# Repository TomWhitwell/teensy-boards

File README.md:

# teensy-boards

## Teensy 3.1 Breakout Board R2

[https://www.oshpark.com/shared_projects/ttl7D5iT](https://www.oshpark.com/shared_projects/ttl7D5iT)

## Teensy 3.2 Breakout Board R3

[https://www.oshpark.com/shared_projects/Gnvbt7io](https://www.oshpark.com/shared_projects/Gnvbt7io)

## Teensy 3.X to 2.2" display adapter T1

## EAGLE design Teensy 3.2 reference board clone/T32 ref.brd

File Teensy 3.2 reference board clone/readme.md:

# Teensy 3 reference board clone

Teensy3 reference board recreated in eagle

shared basket at mouser: http://www.mouser.com/ProjectManager/ProjectDetail.aspx?AccessID=719df5721e

Pre-programmed Bootloader Chip for DIY Teensy LC & 3.2 Projects http://pjrc.com/store/ic_mkl02.html (IC_MKL04Z32_TQFP32)

shared project on osh park: https://www.oshpark.com/shared_projects/h2HB6bQQ

### What is different from the "original" Teensy 3.2 DIY Reference Board

PJRC Teensy 3.2 DIY Reference Board https://www.oshpark.com/shared_projects/d3J03Zeb

- the silkscreen is a bit messed up  
  
- the actuator from the tactile switch is shorter (ALPS	SKHHPKA010)

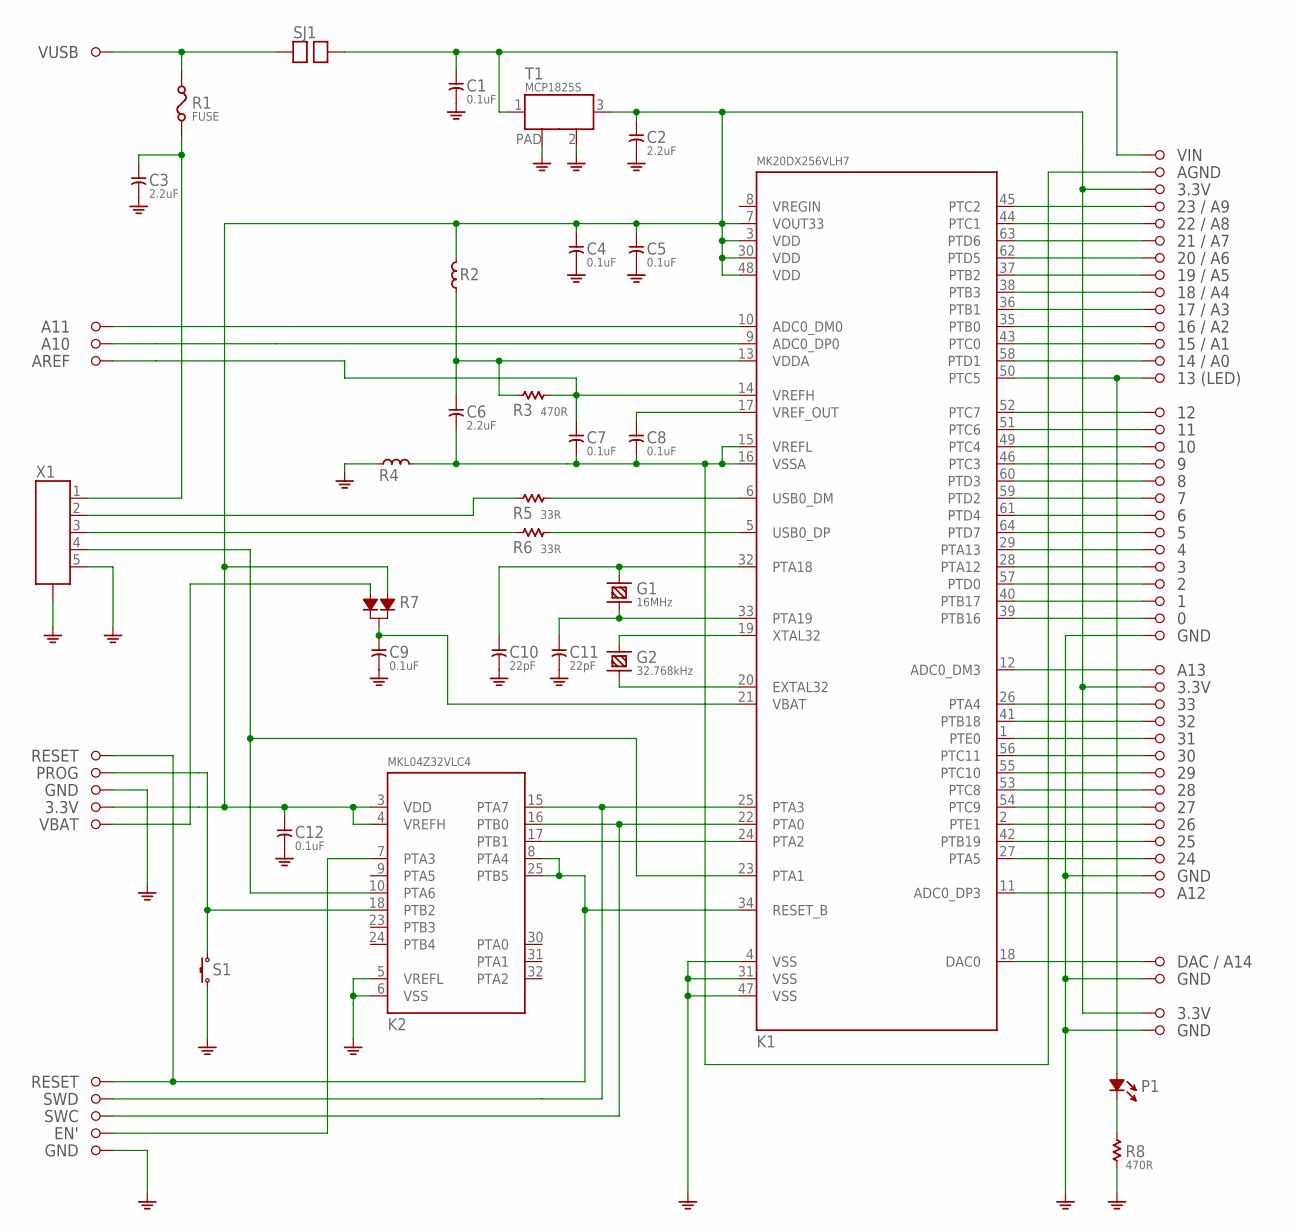
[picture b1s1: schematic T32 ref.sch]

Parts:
C1, C4, C5, C7, C8, C9, C12: 0.1uF; C0603
C2, C3, C6: 2.2uF; C0805
C10, C11: 22pF; C0603
G1: 16MHz; HC49US
G2: 32.768kHz; TC26H
K1: MK20DX256VLH7; LQFP64-05
K2: MKL04Z32VLC4; LQFP32-08
P1: LED; LED-0805
R1: FUSE; F0805
R2, R4: FERRITE; L0603
R3, R8: 470R; R0603
R5, R6: 33R; R0603
R7: DIODE_DUAL; SOT-23
S1: TACT_SWITCH; ALPS_SKHH
SJ1: SOLDERJUMPER
SX1, SX2, SX3, SX4, SX5, SX6, SX7, SX8, SX9, SX10, SX11, SX12, SX13, SX14, SX15, SX16, SX17, SX18, SX19, SX20, SX21, SX22, SX23, SX24, SX25, SX26, SX27, SX28, SX29, SX30, SX31, SX32, SX33, SX34, SX35, SX36, SX37, SX38, SX39, SX40, SX41, SX42, SX43, SX44, SX45, SX46, SX47, SX48, SX49, SX50, SX51, SX52, SX53, SX54, SX55, SX56, SX57, SX58, SX59, SX60: PIN; PTH_39MIL
T1: MCP1825S; SOT-223
X1: MINI-USB; MOLEX_SD-67503-010

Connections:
GND: C1.2, C2.2, C3.2, C4.2, C5.2, C9.2, C10.2, C11.2, C12.2, K1.4 (VSS), K1.31 (VSS), K1.47 (VSS), K2.5 (VREFL), K2.6 (VSS), R4.1, R8.1, S1.3, S1.4 (3), SX32.1, SX42.1, SX50.1, SX53.1, SX55.1, SX60.1, T1.2 (GND), T1.PAD, X1.5, X1.P$1 (CASE), X1.P$2 (CASE), X1.P$3 (CASE), X1.P$4 (CASE), X1.P$5 (CASE), X1.P$6 (CASE)
unnamed: K2.7 (PTA3), SX59.1
unnamed: K1.22 (PTA0), K2.16 (PTB0), SX58.1
unnamed: K1.24 (PTA2), K2.17 (PTB1)
unnamed: C10.1, G1.1, K1.32 (PTA18)
unnamed: C11.1, G1.2, K1.33 (PTA19)
unnamed: G2.2 (1), K1.19 (XTAL32)
unnamed: G2.1 (2), K1.20 (EXTAL32)
unnamed: K2.18 (PTB2), S1.1, S1.2 (1), SX40.1
unnamed: K1.5 (USB0_DP), R6.2
unnamed: C8.1, K1.17 (VREF_OUT)
unnamed: K1.34 (RESET_B), K2.8 (PTA4), K2.25 (PTB5), SX38.1, SX56.1
unnamed: C7.1, K1.14 (VREFH), R3.2, SX16.1
unnamed: K1.6 (USB0_DM), R5.2
unnamed: C6.1, K1.13 (VDDA), R2.1, R3.1
unnamed: R6.1, X1.3
unnamed: R5.1, X1.2
unnamed: C3.1, R1.1, X1.1
unnamed: K1.23 (PTA1), K2.10 (PTA6), X1.4
unnamed: K1.45 (PTC2), SX5.1
unnamed: K1.44 (PTC1), SX6.1
unnamed: K1.63 (PTD6), SX7.1
unnamed: K1.62 (PTD5), SX8.1
unnamed: K1.37 (PTB2), SX9.1
unnamed: K1.38 (PTB3), SX10.1
unnamed: K1.36 (PTB1), SX11.1
unnamed: K1.35 (PTB0), SX13.1
unnamed: K1.43 (PTC0), SX15.1
unnamed: K1.58 (PTD1), SX17.1
unnamed: K1.50 (PTC5), P1.+, SX18.1
unnamed: K1.52 (PTC7), SX19.1
unnamed: K1.51 (PTC6), SX20.1
unnamed: K1.49 (PTC4), SX21.1
unnamed: K1.46 (PTC3), SX22.1
unnamed: K1.60 (PTD3), SX23.1
unnamed: K1.59 (PTD2), SX24.1
unnamed: K1.61 (PTD4), SX25.1
unnamed: K1.64 (PTD7), SX26.1
unnamed: K1.29 (PTA13), SX27.1
unnamed: K1.28 (PTA12), SX28.1
unnamed: K1.57 (PTD0), SX29.1
unnamed: K1.40 (PTB17), SX30.1
unnamed: K1.39 (PTB16), SX31.1
unnamed: K1.12 (ADC0_DM3), SX33.1
unnamed: K1.26 (PTA4), SX35.1
unnamed: K1.41 (PTB18), SX36.1
unnamed: K1.1 (PTE0), SX37.1
unnamed: K1.56 (PTC11), SX39.1
unnamed: K1.55 (PTC10), SX41.1
unnamed: K1.53 (PTC8), SX43.1
unnamed: P1.-, R8.2
unnamed: C6.2, C7.2, C8.2, K1.15 (VREFL), K1.16 (VSSA), R4.2, SX3.1
unnamed: K1.18 (DAC0), SX52.1
unnamed: K1.11 (ADC0_DP3), SX51.1
unnamed: K1.27 (PTA5), SX49.1
unnamed: K1.42 (PTB19), SX48.1
unnamed: K1.2 (PTE1), SX47.1
unnamed: K1.54 (PTC9), SX45.1
unnamed: C1.1, SJ1.2, SX2.1, T1.1 (IN)
unnamed: R7.2, SX46.1
unnamed: K1.10 (ADC0_DM0), SX12.1
unnamed: K1.9 (ADC0_DP0), SX14.1
unnamed: R1.2, SJ1.1, SX1.1
unnamed: C9.1, K1.21 (VBAT), R7.3
unnamed: C2.1, C4.1, C5.1, C12.1, K1.3 (VDD), K1.7 (VOUT33), K1.30 (VDD), K1.48 (VDD), K2.3 (VDD), K2.4 (VREFH), R2.2, R7.1, SX4.1, SX34.1, SX44.1, SX54.1, T1.3 (OUT)
unnamed: K1.25 (PTA3), K2.15 (PTA7), SX57.1

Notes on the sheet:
VIN
AGND
3.3V
23 / A9
22 / A8
21 / A7
20 / A6
19 / A5
18 / A4
17 / A3
16 / A2
15 / A1
14 / A0
13 (LED)
GND
A13
A12
DAC / A14
VBAT
RESET
PROG
A11
A10
AREF
VUSB
SWD
SWC
EN'

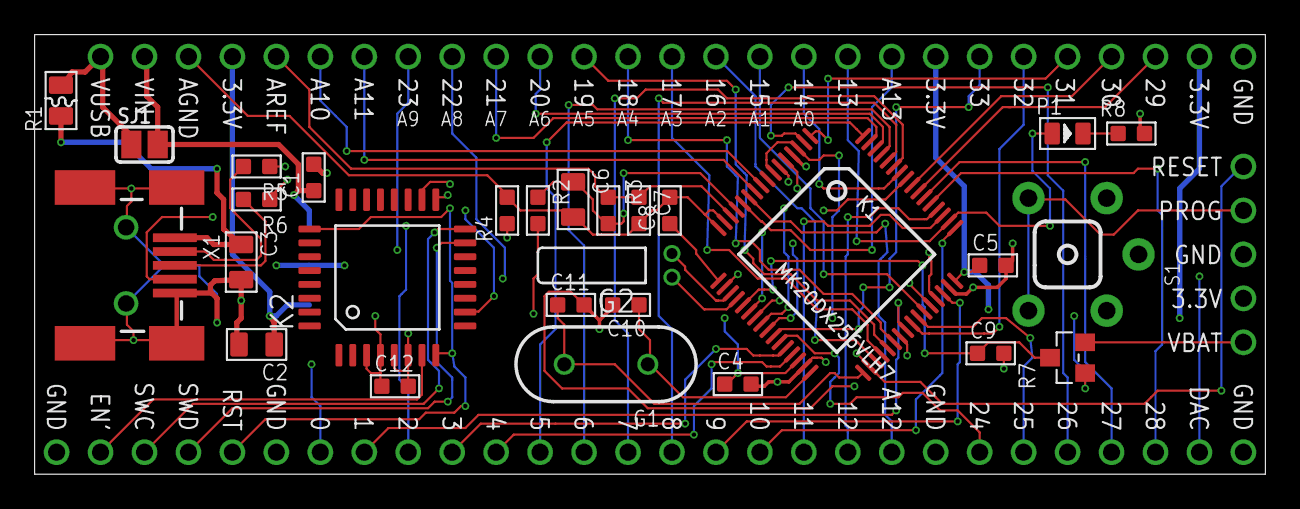
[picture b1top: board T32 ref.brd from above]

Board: 4 copper layers, 71.1 x 25.4 mm, 89 parts (1 on the bottom side), 66 nets.

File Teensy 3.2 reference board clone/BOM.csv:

"Part","TYPE","DESC","PACKAGE","MF","MPN","OC_MOUSER"
"C1","Capacitor","0.1uF / 10VDC /  X7R ","0603","Murata Electronics","GRM155R71A104KA01D","81-GRM155R71A104KA1D"
"C2","Capacitor","2.2uF / 25 VDC / X7R ","0805","Taiyo Yuden","TMK212B7225KG-TR","963-TMK212B7225KG-TR"
"C3","Capacitor","2.2uF / 25 VDC / X7R ","0805","Taiyo Yuden","TMK212B7225KG-TR","963-TMK212B7225KG-TR"
"C4","Capacitor","0.1uF / 10VDC /  X7R ","0603","Murata Electronics","GRM155R71A104KA01D","81-GRM155R71A104KA1D"
"C5","Capacitor","0.1uF / 10VDC /  X7R ","0603","Murata Electronics","GRM155R71A104KA01D","81-GRM155R71A104KA1D"
"C6","Capacitor","2.2uF / 25 VDC / X7R ","0805","Taiyo Yuden","TMK212B7225KG-TR","963-TMK212B7225KG-TR"
"C7","Capacitor","0.1uF / 10VDC /  X7R ","0603","Murata Electronics","GRM155R71A104KA01D","81-GRM155R71A104KA1D"
"C8","Capacitor","0.1uF / 10VDC /  X7R ","0603","Murata Electronics","GRM155R71A104KA01D","81-GRM155R71A104KA1D"
"C9","Capacitor","0.1uF / 10VDC /  X7R ","0603","Murata Electronics","GRM155R71A104KA01D","81-GRM155R71A104KA1D"
"C10","Capacitor","22pF / 50VDC / C0G (NP0)","0603","Vishay / Vitramon","VJ0603A220JXACW1BC","77-VJ0603A220JXACBC"
"C11","Capacitor","22pF / 50VDC / C0G (NP0)","0603","Vishay / Vitramon","VJ0603A220JXACW1BC","77-VJ0603A220JXACBC"
"C12","Capacitor","0.1uF / 10VDC /  X7R ","0603","Murata Electronics","GRM155R71A104KA01D","81-GRM155R71A104KA1D"
"G1","Crystal","16MHz / 18pF / 10ppm","HC-49US","ABRACON","ABL-16.000MHz-B1U","815-ABL-16-B1U"
"G2","Crystal","32.768kHz / 12.5pF / 20ppm","TC-26H","Citizen FineDevice"," CFS206-32.768KDZF-UB","695-CFS206-327KF-U"
"K1","Microcontroller","MK20DX256VLH7","LQFP-64","NXP","MK20DX256VLH7","841-MK20DX256VLH7"
"K2","Microcontroller","MKL04Z32VLC4 (preprogrammed)","LQFP-32","PJRC","IC_MKL04Z32_TQFP32",
"P1","LED","orange","0805","ROHM Semiconductor","SML-211DTT86","755-SML-211DTT86"
"R1","PPTC","6V / 0.5A","0805","Bel Fuse","0ZCK0050FF2E","530-0ZCK0050FF2E"
"R2","Ferrite","600R / 100MHz","0603","Murata Electronics"," BLM18AG601SN1D","81-BLM11A601S"
"R3","Resistor","470R / 1 % /  0.1 W","0603","Vishay","CRCW0603470RFKEA","71-CRCW0603-470-E3"
"R4","Ferrite","600R / 100MHz","0603","Murata Electronics"," BLM18AG601SN1D","81-BLM11A601S"
"R5","Resistor","33R / 1% / 0.25 W","0603","Panasonic","ERJ-PA3F33R0V","667-ERJ-PA3F33R0V"
"R6","Resistor","33R / 1% / 0.25 W","0603","Panasonic","ERJ-PA3F33R0V","667-ERJ-PA3F33R0V"
"R7","Diode","Dual Schottky, common cat","SOT-23","NXP Semiconductors","BAT54C,215","771-BAT54C-T/R"
"R8","Resistor","470R / 1 % /  0.1 W","0603","Vishay","CRCW0603470RFKEA","71-CRCW0603-470-E3"
"S1","Tactile switch","SPST","6x6x5 MM","ALPS","SKHHPKA010","688-SKHHPK"
"T1","Voltage regulator","3.3V 500mA","SOT-223-3","Microchip Technology","MCP1825S-3302E/DB","579-MCP1825S-3302EDB"
"X1","Mini USB","MINI USB",,"MOLEX","675031020","538-67503-1020"

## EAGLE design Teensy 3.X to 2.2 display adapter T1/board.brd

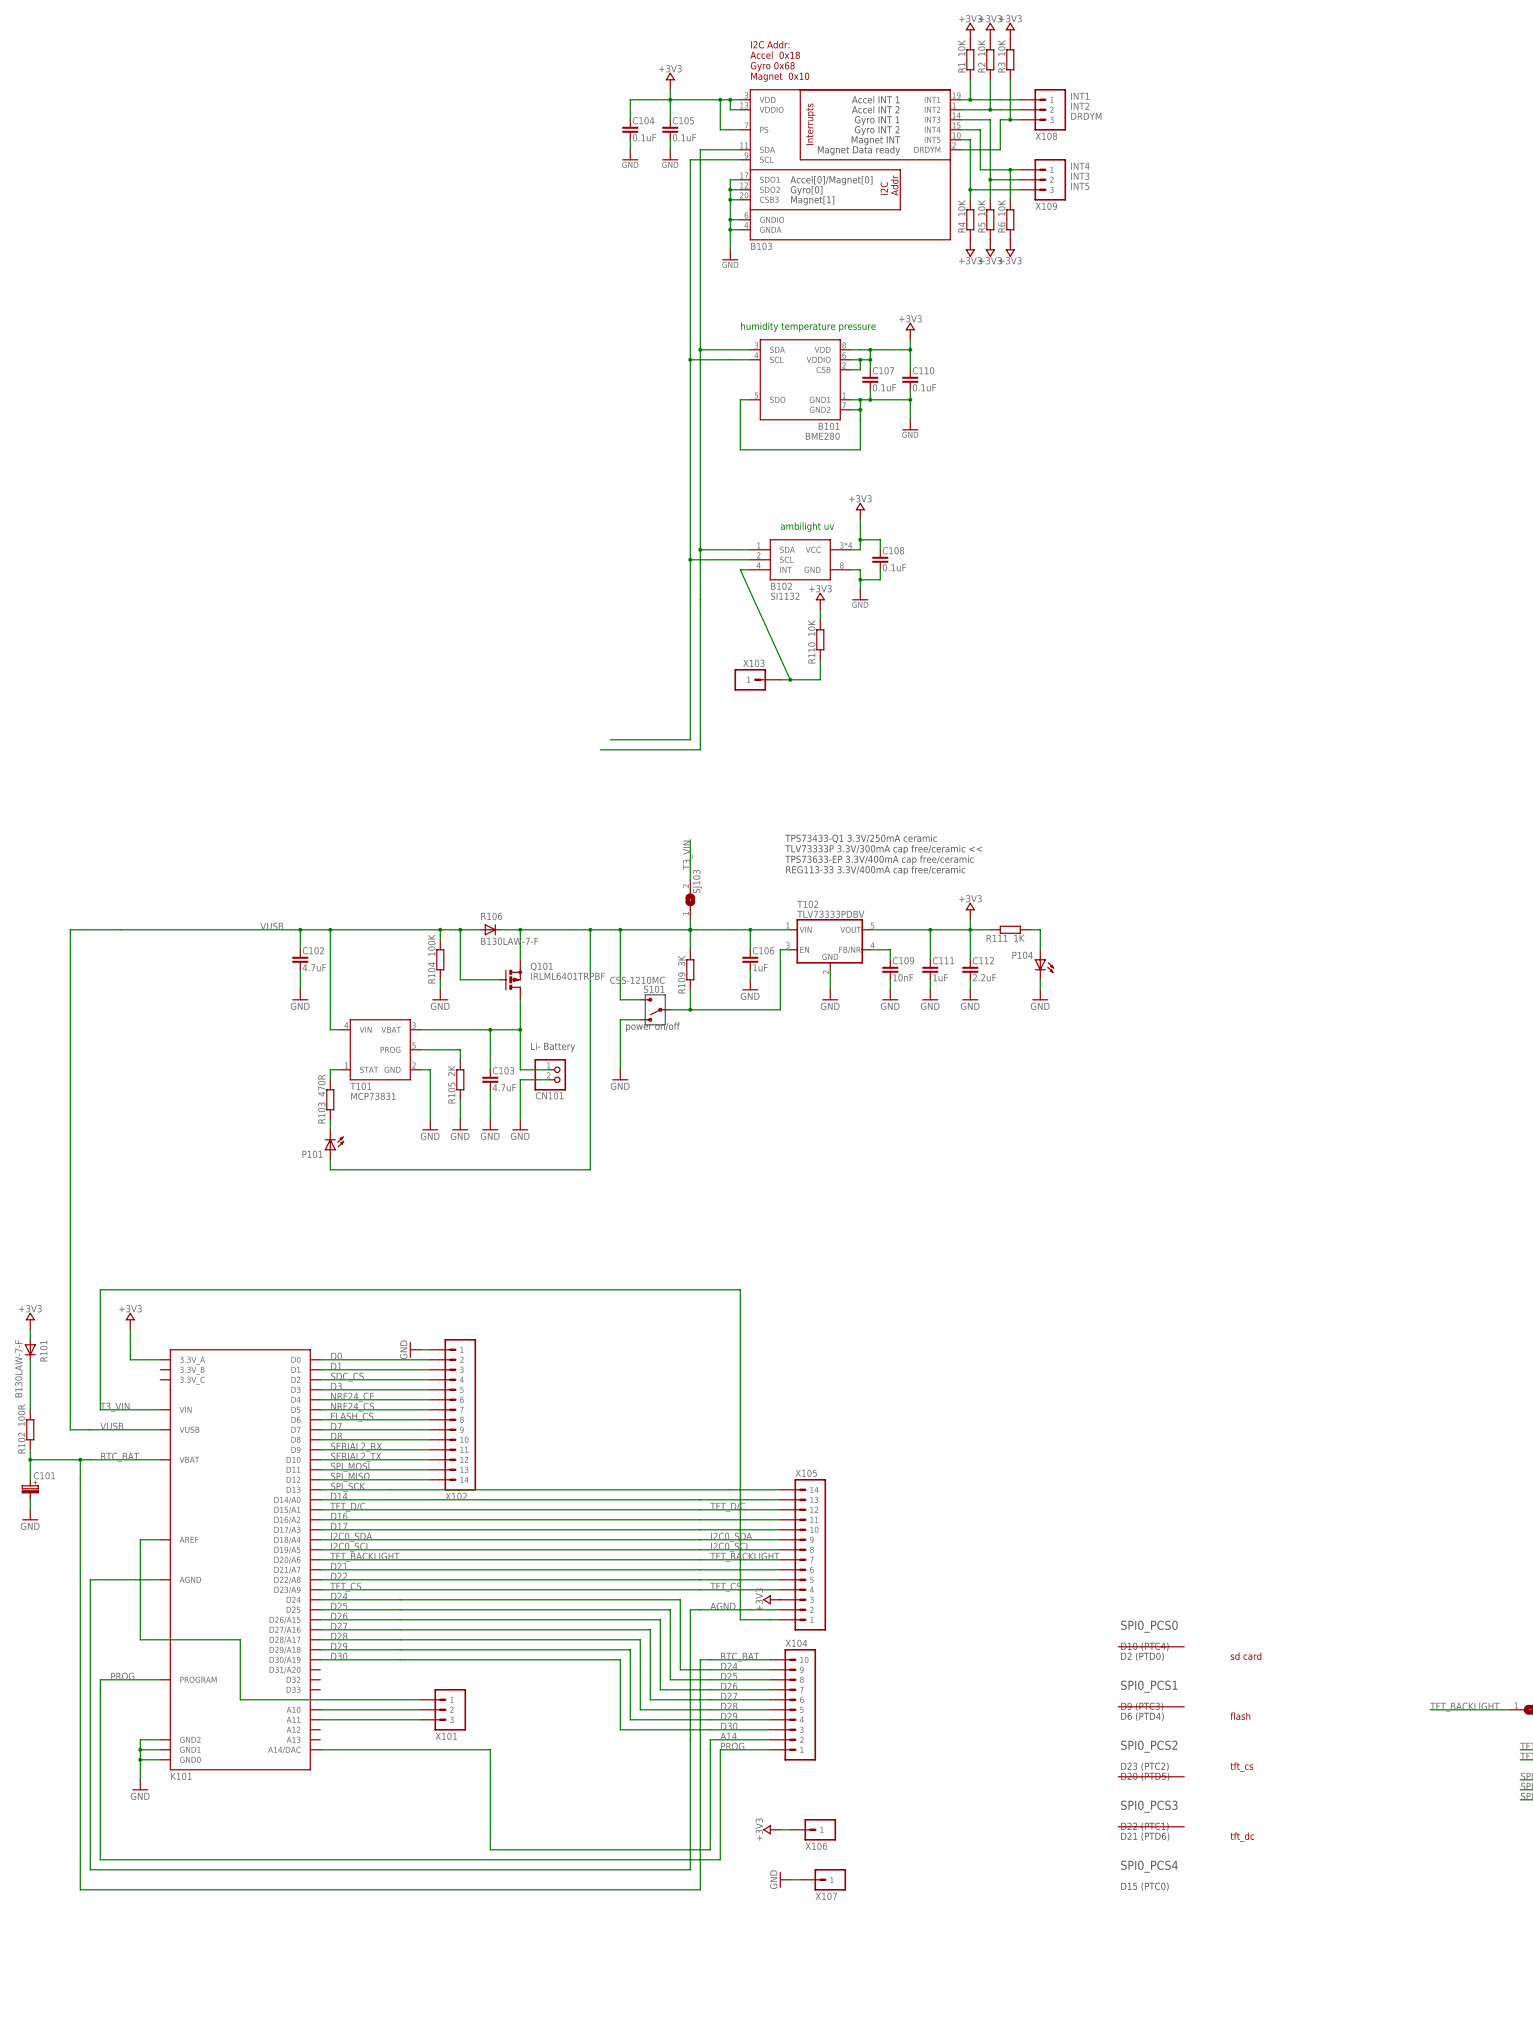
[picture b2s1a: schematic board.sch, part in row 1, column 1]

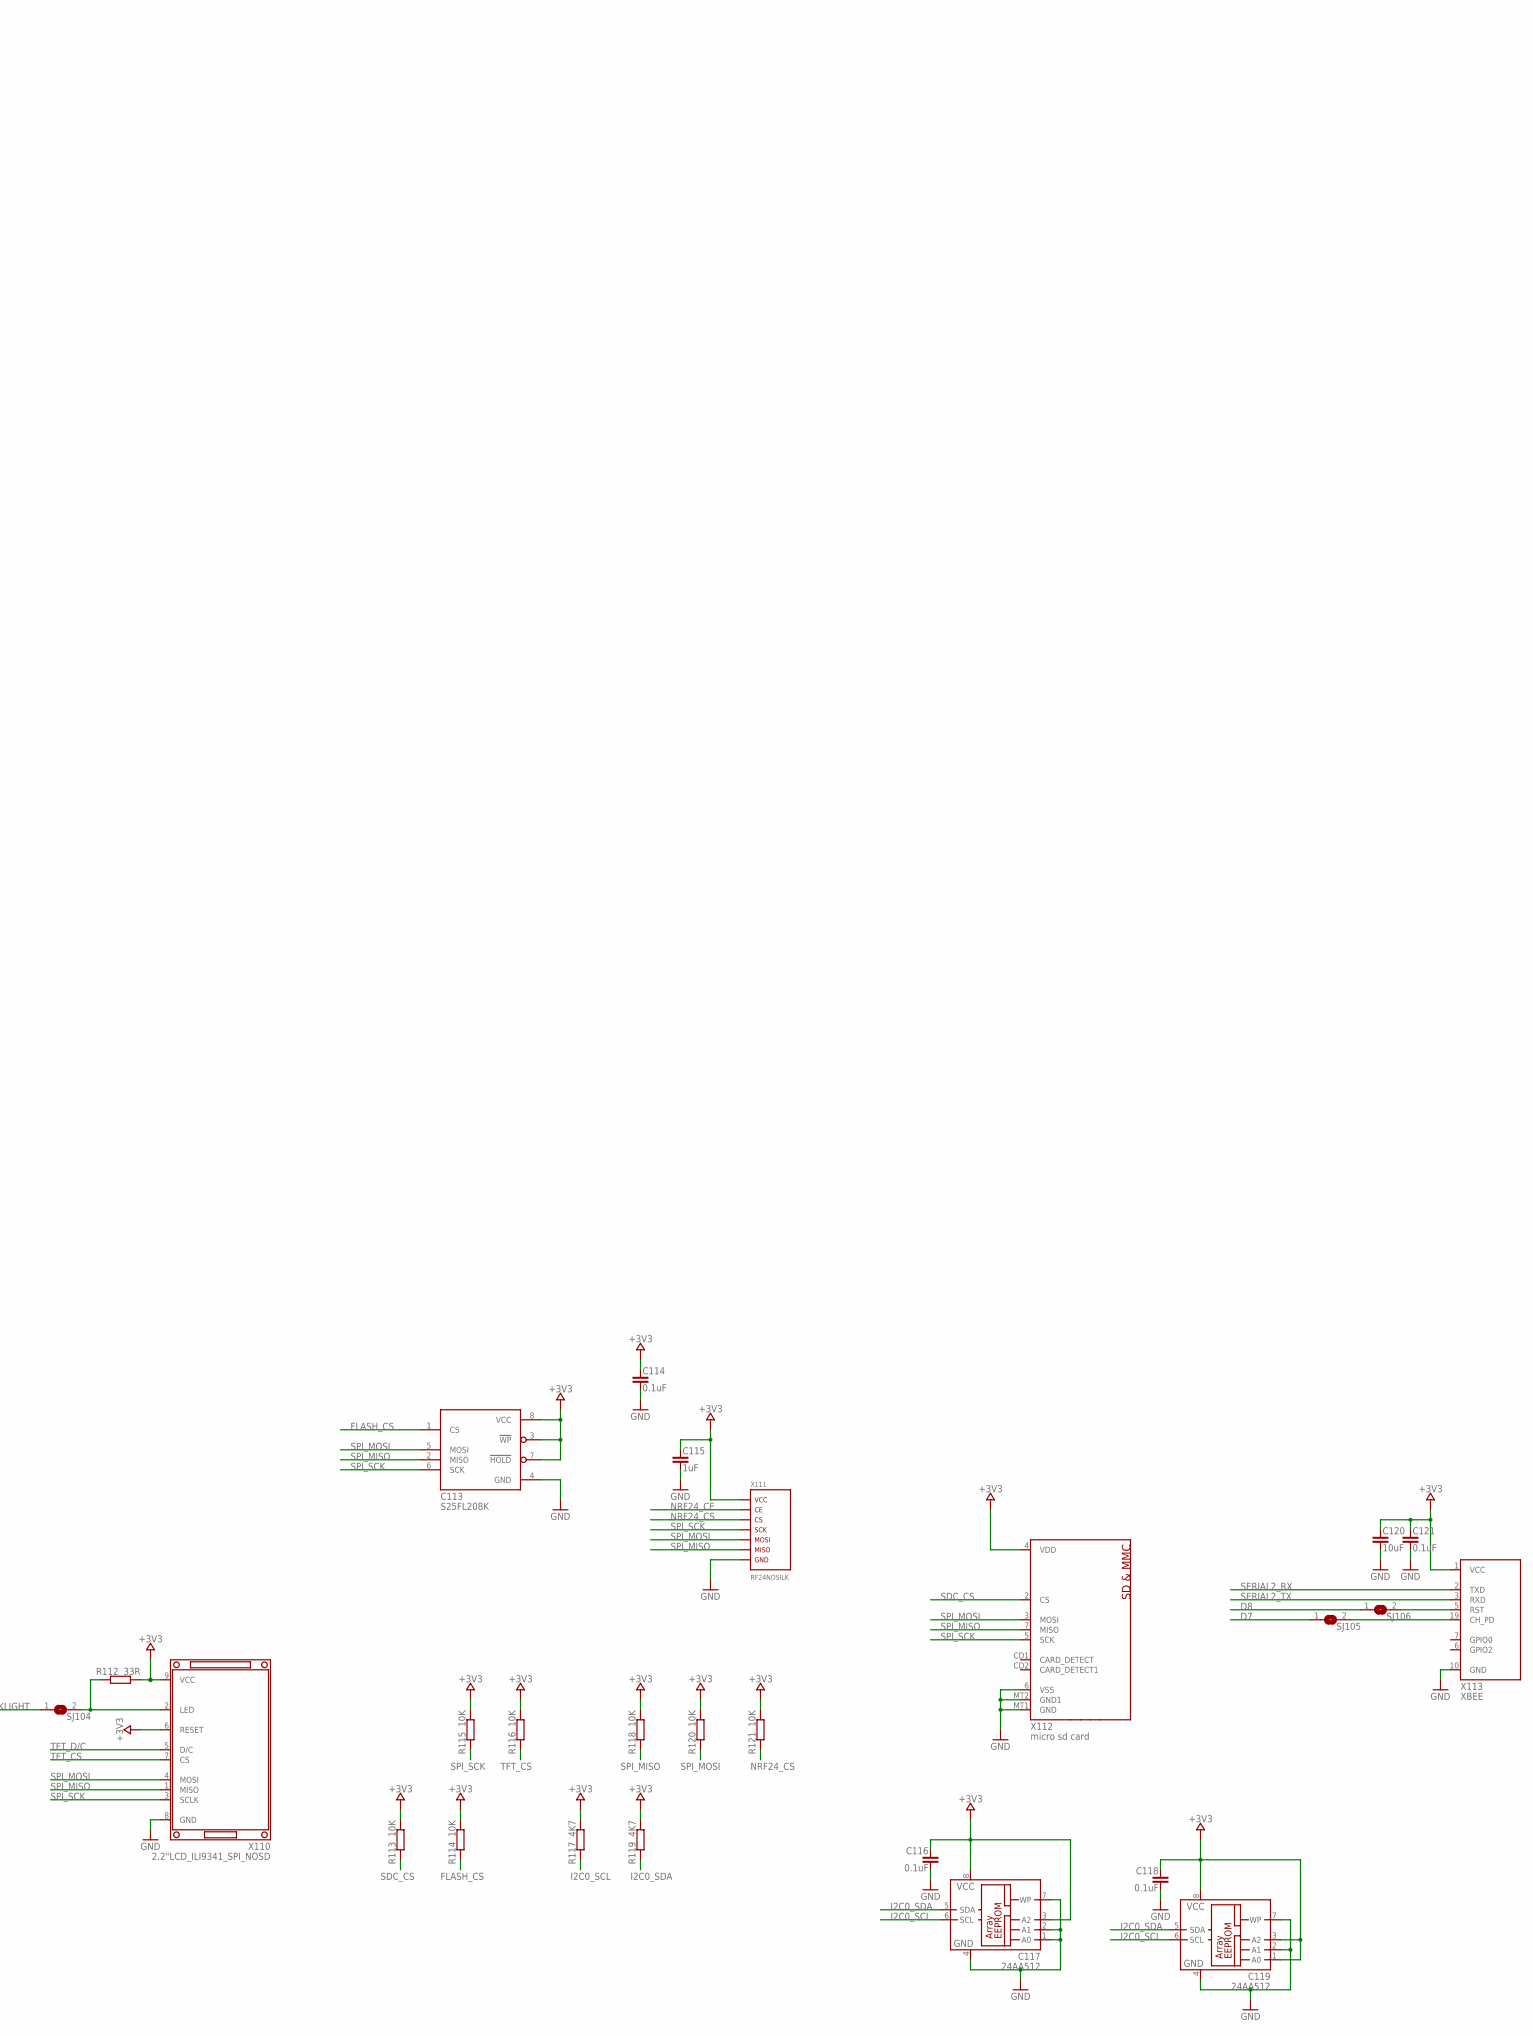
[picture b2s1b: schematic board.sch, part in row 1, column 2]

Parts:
B101: BME280; BOSCH_8LGA_0.35X0.35
B102: SI1132; SILABS_QFN-10_(ONLY_8PAD)
B103: BMX055; BMX055_LGA20
C101: CAPACITOR_POLCPH3225A; CPH3225A
C102, C103: 4.7uF; SMT_M2012(0805)_G1; MPN 0805ZD475KAT2A
C104, C105, C107, C108, C110, C114, C116, C118, C121: 0.1uF; SMT_M1608(0603)_G1; MPN 0603YC104K4Z2A
C106, C111, C115: 1uF; SMT_M1608(0603)_G1; MPN 0603ZD105KAT2A
C109: 10nF; SMT_M1608(0603)_G1; MPN MC0603B103K500CT
C112: 2.2uF; SMT_M2012(0805)_G1; MPN C1206C226K9PACTU
C113: S25FL208K; SOIC-8; MPN S25FL208K0RMFI041
C117, C119: 24AA512; SOIC-8; MPN 24AA512-I/SM
C120: 10uF; SMT_M2012(0805)_G1; MPN MCTT31F106Z100CT
CN101: JST_2PIN-SMT-RA; JST-PH-2-SMT-RA; MPN S2B-PH-SM4-TB(LF)(SN)
K101: TEENSY3.1_ALLPINSNOSILK; TEENSY3.1_ALLPINS/NOSILK
P101, P104: LEDSMT_M1608(0603)_LED_G1; SMT_M1608(0603)_LED_G1; MPN TLMS1100-GS08
Q101: IRLML6401TRPBF; SOT23-SPEC1; MPN IRLML6401TRPBF
R1, R2, R3, R4, R5, R6, R113, R114, R115, R116, R118, R120, R121: 10K; SMT_M1608(0603)_G1; MPN CRCW060310K0FKEA
R101, R106: B130LAW-7-F; SOD123V2; MPN B130LAW-7-F
R102: 100R; SMT_M1608(0603)_G1; MPN CRCW060310K0FKEA
R103: 470R; SMT_M1608(0603)_G1; MPN CRCW0603470RFKEA
R104: 100K; SMT_M1608(0603)_G1; MPN CRCW060310K0FKEA
R105: 2K; SMT_M1608(0603)_G1; MPN CRCW06032K00FKEA
R109: 3K; SMT_M1608(0603)_G1; MPN CRCW06033K00FKEA
R110: 10K; SMT_M1608(0603)_G1
R111: 1K; SMT_M1608(0603)_G1; MPN CRCW0603330RFKEA
R112: 33R; SMT_M1608(0603)_G1; MPN CRCW0805100RFKEA
R117, R119: 4K7; SMT_M1608(0603)_G1; MPN CRCW06034K70FKEA
S101: CSS-1210MC; CSS-1210(M)C
SJ103, SJ104: n/a; SMT_M1608(0603)_G1
SJ105, SJ106: 0R; SMT_M1608(0603)_G1
T101: MCP73831; SOT23-5_MICROCHIP; MPN MCP73831T-2ATI/OT
T102: TLV73333PDBV; R-PDSO-G5; MPN TLV73333PDBVT
X101, X108, X109: 3P1/MIN_SILK2; HEADER_1X3_1/MIN_SILK2
X102, X105: 14P1/MIN_SILK2; HEADER_1X14_1/MIN_SILK2
X103, X106, X107: 1P1/MIN_SILK2; HEADER_1X1_1/MIN_SILK2
X104: 10P1X10P_1/MIN_SILK2; HEADER_1X10_1/MIN_SILK2
X110: 2.2"LCD_ILI9341_SPI_NOSD; 2.2_TFT1
X111: RF24NOSILK; RF24_NOSILK
X112: micro sd card; MICROSD; MPN MEM2051-00-195-00-A.
X113: XBEE; ESP_BEE_PTH_VCC_GND_RX_TX_PD_RST_IO0_IO2

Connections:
3.3V_B: K101.3V3_B (3.3V_B)
3.3V_C: K101.3V3_C (3.3V_C)
+3V3: B101.2 (CSB), B101.6 (VDDIO), B101.8 (VDD), B102.3 (VCC), B102.6 (VCC), B102.7 (VCC), B102.9 (VCC), B103.3 (VDD), B103.7 (PS), B103.13 (VDDIO), C104.1, C105.1, C107.1, C108.1, C110.1, C111.1, C112.1, C113.3 (!WP), C113.7 (!HOLD), C113.8 (VCC), C114.1, C115.1, C116.1, C117.3 (A2), C117.8 (VCC), C118.1, C119.1 (A0), C119.3 (A2), C119.8 (VCC), C120.1, C121.1, K101.3V3_A (3.3V_A), R1.2, R2.2, R3.2, R4.1, R5.1, R6.1, R101.A, R110.2, R111.1, R112.2, R113.2, R114.2, R115.2, R116.2, R117.2, R118.2, R119.2, R120.2, R121.2, T102.5 (VOUT), X105.3, X106.1, X110.6 (RESET), X110.9 (VCC), X111.VCC, X112.4 (VDD), X113.1 (VCC)
A14: K101.A14 (A14/DAC), X104.2
AGND: K101.AGND, X105.2
BAT_CHG_OUT: C106.1, P101.A, Q101.2 (S), R106.K (C), R109.2, S101.2 (S), SJ103.1, T102.1 (VIN)
D0: K101.D0, X102.2
D1: K101.D1, X102.3
D3: K101.D3, X102.5
D7: K101.D7, SJ105.1, X102.9
D8: K101.D8, SJ106.1, X102.10
D14: K101.A0 (D14/A0), X105.13
D16: K101.A2 (D16/A2), X105.11
D17: K101.A3 (D17/A3), X105.10
D21: K101.A7 (D21/A7), X105.6
D22: K101.A8 (D22/A8), X105.5
D24: K101.D24, X104.9
D25: K101.D25, X104.8
D26: K101.D26 (D26/A15), X104.7
D27: K101.D27 (D27/A16), X104.6
D28: K101.D28 (D28/A17), X104.5
D29: K101.D29 (D29/A18), X104.4
D30: K101.D30 (D30/A19), X104.3
DRDYM: B103.2 (DRDYM), R3.1, X108.3
ENABLE_POWER: R109.1, S101.3, T102.3 (EN)
FLASH_CS: C113.1 (CS), K101.D6, R114.1, X102.8
GND: B101.1 (GND1), B101.5 (SDO), B101.7 (GND2), B102.8 (GND), B103.4 (GNDA), B103.6 (GNDIO), B103.12 (SDO2), B103.17 (SDO1), B103.20 (CSB3), C101.-, C102.2, C103.2, C104.2, C105.2, C106.2, C107.2, C108.2, C109.2, C110.2, C111.2, C112.2, C113.4 (GND), C114.2, C115.2, C116.2, C117.1 (A0), C117.2 (A1), C117.4 (GND), C117.7 (WP), C118.2, C119.2 (A1), C119.4 (GND), C119.7 (WP), C120.2, C121.2, CN101.2 (1), K101.GND0, K101.GND1, K101.GND2, P104.C, R104.1, R105.1, S101.1 (O), T101.2 (GND), T102.2 (GND), X102.1, X107.1, X110.8 (GND), X111.GND, X112.6 (VSS), X112.MT1 (GND), X112.MT2 (GND1), X113.10 (GND)
I2C0_SCL: B101.4 (SCL), B102.2 (SCL), B103.9 (SCL), C117.6 (SCL), C119.6 (SCL), K101.A5 (D19/A5), R117.1, X105.8
I2C0_SDA: B101.3 (SDA), B102.1 (SDA), B103.11 (SDA), C117.5 (SDA), C119.5 (SDA), K101.A4 (D18/A4), R119.1, X105.9
INT1: B103.19 (INT1), R1.1, X108.1
INT2: B103.1 (INT2), R2.1, X108.2
INT3: B103.14 (INT3), R5.2, X109.2
INT4: B103.15 (INT4), R6.2, X109.1
INT5: B103.10 (INT5), R4.2, X109.3
IO3: B102.4 (INT), R110.1, X103.1
unnamed: R105.2, T101.5 (PROG)
unnamed: R103.2, T101.1 (STAT)
unnamed: P101.C, R103.1
unnamed: P104.A, R111.2
unnamed: SJ106.2, X113.5 (RST)
unnamed: R101.K (C), R102.2
unnamed: SJ105.2, X113.19 (CH_PD)
unnamed: K101.A11, X101.3
unnamed: K101.A10, X101.2
unnamed: K101.AREF, X101.1
unnamed: R112.1, SJ104.2, X110.2 (LED)
unnamed: C109.1, T102.4 (FB/NR)
NRF24_CE: K101.D4, X102.6, X111.CE
NRF24_CS: K101.D5, R121.1, X102.7, X111.CS
PROG: K101.PROG (PROGRAM), X104.1
RTC_BAT: C101.+, K101.VBAT, R102.1, X104.10
SDC_CS: K101.D2, R113.1, X102.4, X112.2 (CS)
SERIAL2_RX: K101.D9, X102.11, X113.2 (TXD)
SERIAL2_TX: K101.D10, X102.12, X113.3 (RXD)
SPI_MISO: C113.2 (MISO), K101.D12, R118.1, X102.14, X110.1 (MISO), X111.MISO, X112.7 (MISO)
SPI_MOSI: C113.5 (MOSI), K101.D11, R120.1, X102.13, X110.4 (MOSI), X111.MOSI, X112.3 (MOSI)
SPI_SCK: C113.6 (SCK), K101.D13, R115.1, X105.14, X110.3 (SCLK), X111.SCK, X112.5 (SCK)
T3_VIN: K101.VIN, SJ103.2, X105.1
TFT_BACKLIGHT: K101.A6 (D20/A6), SJ104.1, X105.7
TFT_CS: K101.A9 (D23/A9), R116.1, X105.4, X110.7 (CS)
TFT_D/C: K101.A1 (D15/A1), X105.12, X110.5 (D/C)
VBAT: C103.1, CN101.1 (2), Q101.3 (D), T101.3 (VBAT)
VUSB: C102.1, K101.VUSB, Q101.1 (G), R104.2, R106.A, T101.4 (VIN)

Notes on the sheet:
Li- Battery
power on/off
TPS73433-Q1 3.3V/250mA ceramic TLV73333P 3.3V/300mA cap free/ceramic << TPS73633-EP 3.3V/400mA cap free/ceramic REG113‑33 3.3V/400mA cap free/ceramic
SPI0_PCS0
SPI0_PCS1
SPI0_PCS2
SPI0_PCS3
SPI0_PCS4
D10 (PTC4)
D2 (PTD0)
D9 (PTC3)
D6 (PTD4)
D23 (PTC2)
D20 (PTD5)
D22 (PTC1)
D21 (PTD6)
D15 (PTC0)
sd card
tft_dc
tft_cs
flash
humidity temperature pressure
ambilight uv
I2C Addr: Accel 0x18 Gyro 0x68 Magnet 0x10

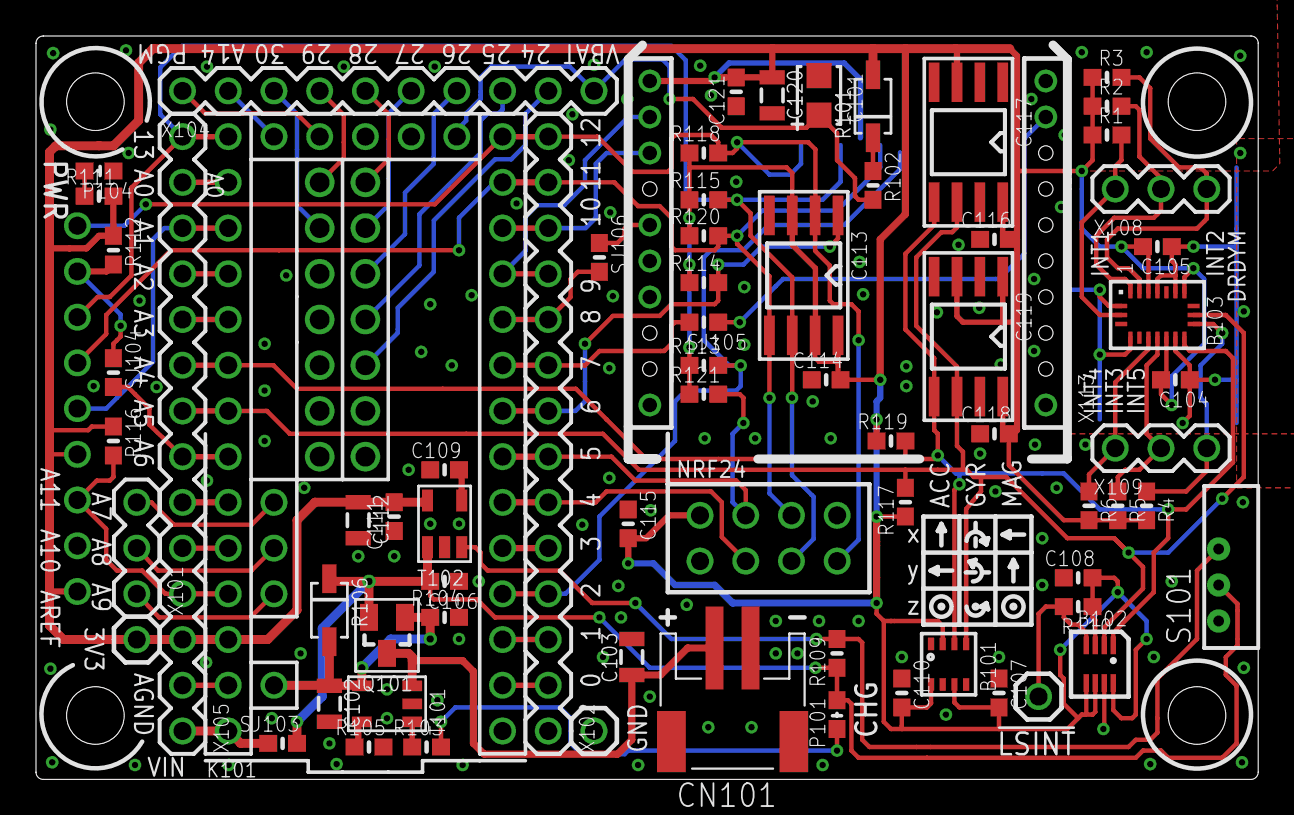
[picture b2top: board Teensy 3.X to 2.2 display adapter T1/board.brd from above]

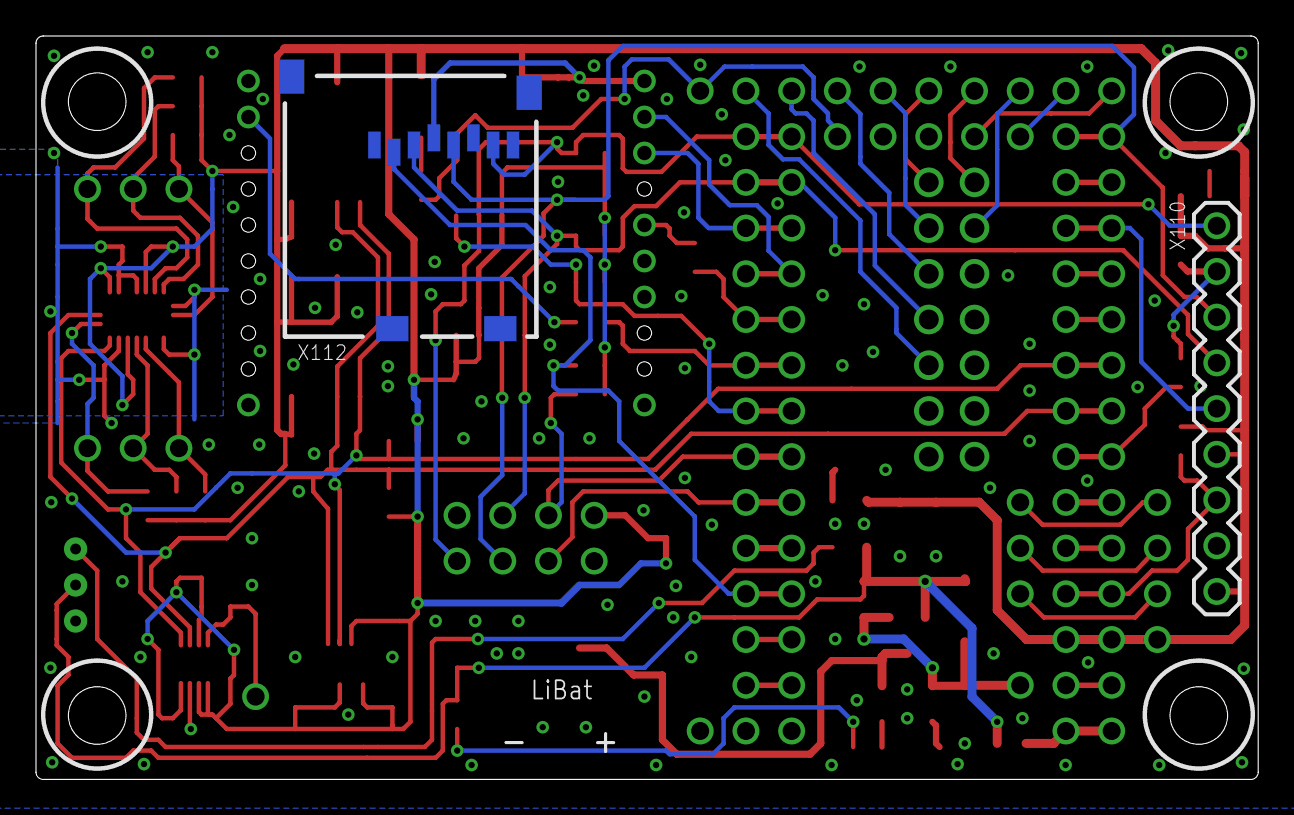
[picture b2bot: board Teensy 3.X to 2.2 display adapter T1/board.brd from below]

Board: 2 copper layers, 67.9 x 41.3 mm, 74 parts (2 on the bottom side), 61 nets.

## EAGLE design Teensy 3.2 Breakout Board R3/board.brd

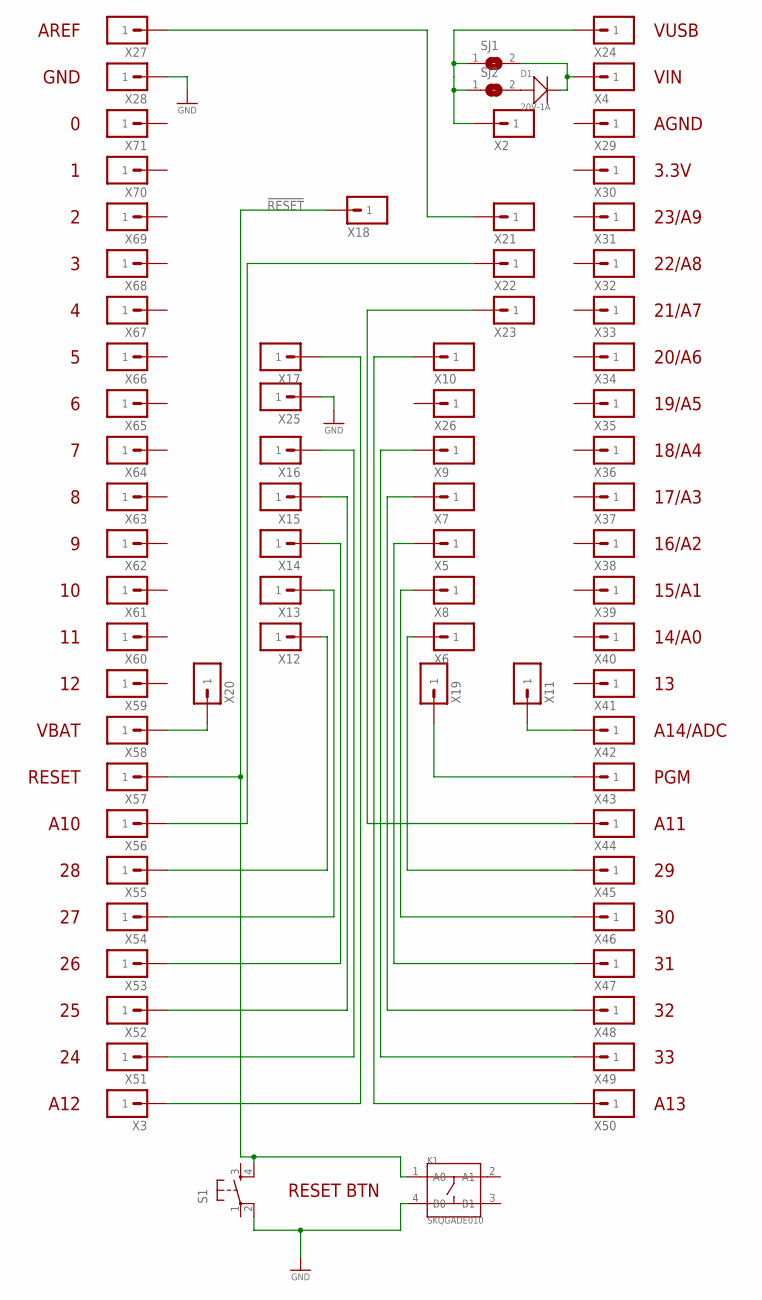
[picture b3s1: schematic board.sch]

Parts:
D1: 20V-1A; SOD-123
K1: SKQGADE010; SW4-SMD-5.2X5.2X1.5MM
S1: SWITCHPTH_NOSILK; SWITCH_PTH_NOSILK
SJ1, SJ2: SOLDERJUMPER; SOLDERJUMPER_ARROW_NOPASTE
X2, X3, X4, X11, X19, X20, X21, X22, X23, X24, X27, X28, X29, X30, X31, X32, X33, X34, X35, X36, X37, X38, X39, X40, X41, X42, X43, X44, X45, X46, X47, X48, X49, X50, X51, X52, X53, X54, X55, X56, X57, X58, X59, X60, X61, X62, X63, X64, X65, X66, X67, X68, X69, X70, X71: 1P1/MIN_NOSILK; HEADER_1X1_1/MIN_NOSILK
X5, X6, X7, X8, X9, X10, X12, X13, X14, X15, X16, X17, X18, X25, X26: 1P; 1P_X

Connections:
!RESET: K1.1 (A0), S1.4, X18.1, X57.1
GND: K1.4 (B0), S1.2, X25.1, X28.1
unnamed: X20.1, X58.1
unnamed: D1.+, SJ2.2
unnamed: X23.1, X44.1
unnamed: SJ1.1, SJ2.1, X2.1, X24.1
unnamed: X3.1, X17.1
unnamed: X16.1, X51.1
unnamed: X15.1, X52.1
unnamed: X14.1, X53.1
unnamed: X13.1, X54.1
unnamed: X12.1, X55.1
unnamed: X21.1, X27.1
unnamed: X10.1, X50.1
unnamed: X9.1, X49.1
unnamed: X7.1, X48.1
unnamed: X5.1, X47.1
unnamed: X8.1, X46.1
unnamed: X6.1, X45.1
unnamed: D1.-, SJ1.2, X4.1
unnamed: X11.1, X42.1
unnamed: X19.1, X43.1
unnamed: X22.1, X56.1

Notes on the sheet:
VUSB
VIN
AGND
3.3V
23/A9
22/A8
21/A7
20/A6
19/A5
18/A4
17/A3
16/A2
15/A1
14/A0
A14/ADC
PGM
A11
A13
A12
A10
RESET
VBAT
GND
AREF
RESET BTN

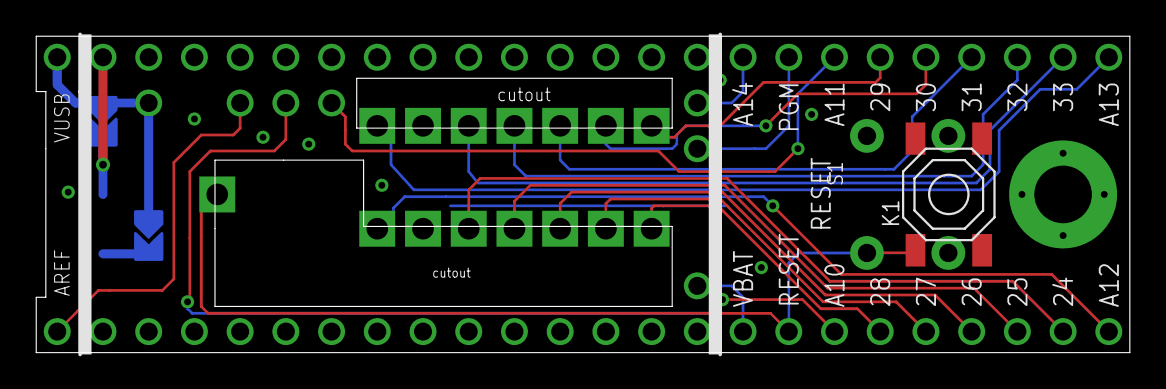
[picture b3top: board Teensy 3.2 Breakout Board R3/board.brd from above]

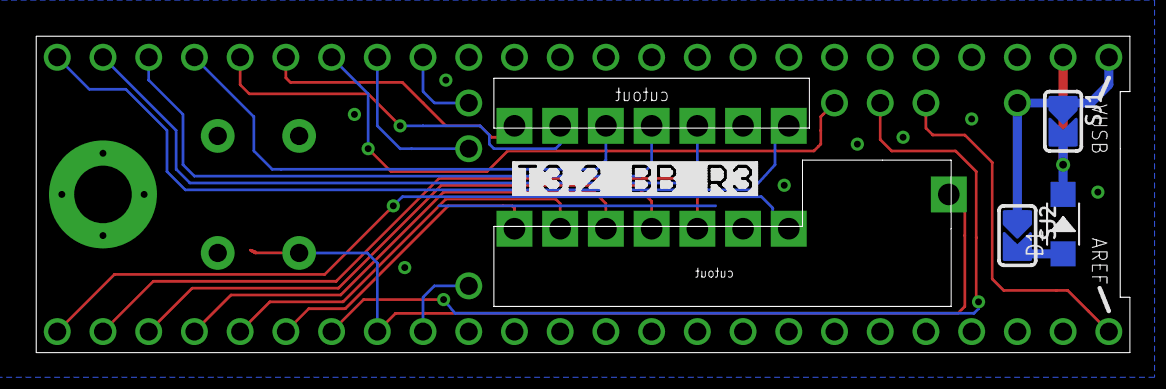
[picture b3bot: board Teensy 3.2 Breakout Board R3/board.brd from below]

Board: 2 copper layers, 60.8 x 17.6 mm, 76 parts (4 on the bottom side), 23 nets.

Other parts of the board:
U$2: NEG_T3.2_BB_R3

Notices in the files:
parts and their libraries:
microbuilder: This work is placed in the public domain, and may be freely used for commercial and non-commercial work with the following conditions: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
SparkFun-Aesthetics: Licensing: CC v3.0 Share-Alike You are welcome to use this library for commercial purposes.
